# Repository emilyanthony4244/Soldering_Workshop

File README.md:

# Soldering_Workshop
Soldering Workshop design files for teaching at makerspaces and conventions.

# Schematic

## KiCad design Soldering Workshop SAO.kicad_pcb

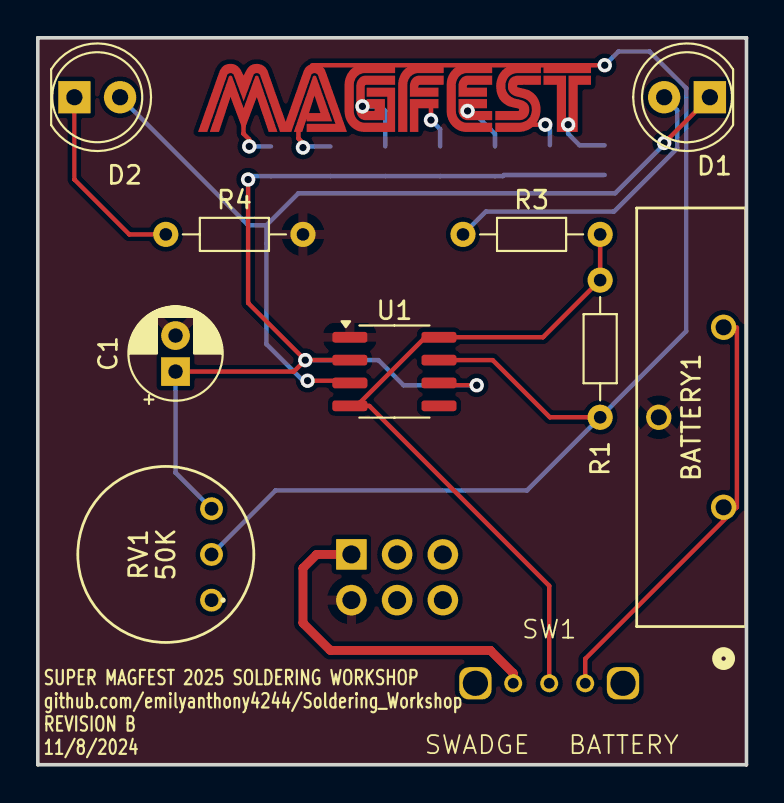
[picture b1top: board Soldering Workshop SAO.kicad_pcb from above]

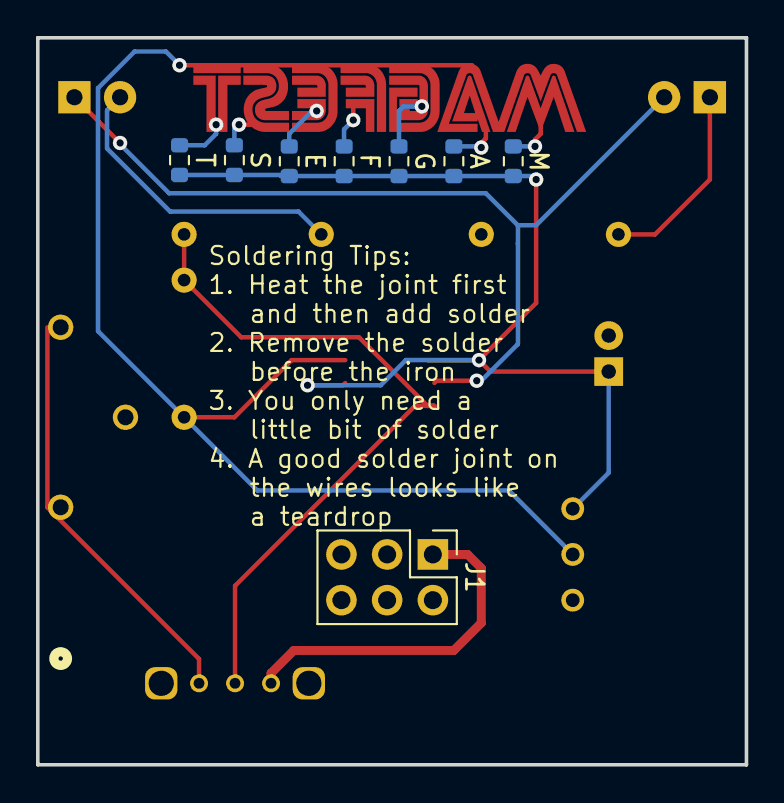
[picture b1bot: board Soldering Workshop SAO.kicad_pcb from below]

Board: 2 copper layers, 39.4 x 40.4 mm, 18 parts (8 on the bottom side), 9 nets.

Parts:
A: R_0603_1608Metric
BATTERY1: 1775485-2; CONN3_1775485-1_TEC
C1: 10uF; CP_Radial_D5.0mm_P2.00mm
D1, D2: LED; LED_D5.0mm
E: R_0603_1608Metric
F: R_0603_1608Metric
G: R_0603_1608Metric
J1: Conn_02x03_Odd_Even; PinHeader_2x03_P2.54mm_Vertical
M: R_0603_1608Metric
R1: 1K; R_Axial_DIN0204_L3.6mm_D1.6mm_P7.62mm_Horizontal
R3, R4: 220; R_Axial_DIN0204_L3.6mm_D1.6mm_P7.62mm_Horizontal
RV1: 50K; 91AR50KLF
S: R_0603_1608Metric
SW1: SW_SPDT; SLW-864574-5A-RA-N-D
T: R_0603_1608Metric
U1: LMC555xM; SOIC-8_3.9x4.9mm_P1.27mm

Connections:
+3V3: R1.1, R3.2, SW1.2 (B), U1.4 (R), U1.8 (VCC)
GND: BATTERY1.2, C1.2, J1.2 (GND), R4.2, U1.1 (GND)
unnamed: D1.2 (A), R3.1
unnamed: D1.1 (K), D2.2 (A), U1.3 (Q)
unnamed: D2.1 (K), R4.1
unnamed: BATTERY1.1, BATTERY1.3, SW1.3 (C)
unnamed: R1.2, RV1.2, U1.7 (DIS)
unnamed: A.2, C1.1, E.2, F.2, G.2, M.2, RV1.3, S.2, T.2, U1.2 (TR), U1.6 (THR)
VCC: J1.1 (VCC), SW1.1 (A)

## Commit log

2024-11-01 Rev A
    Rev A sent to PCBway
2024-11-08 Revision B
    do not blindly trust schematics you find on the internet
    Connect Th to Tr
    Disconnect RV1 from GND
    Connect RV1 to Th
    Flip D1
    Put D1 on silk
2024-11-15 Rev B
2025-01-15 instruction sheets
2025-02-14 cleanup data, readme

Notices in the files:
parts and their libraries:
Copyright 2016 Accelerated Designs. All rights reserved.
